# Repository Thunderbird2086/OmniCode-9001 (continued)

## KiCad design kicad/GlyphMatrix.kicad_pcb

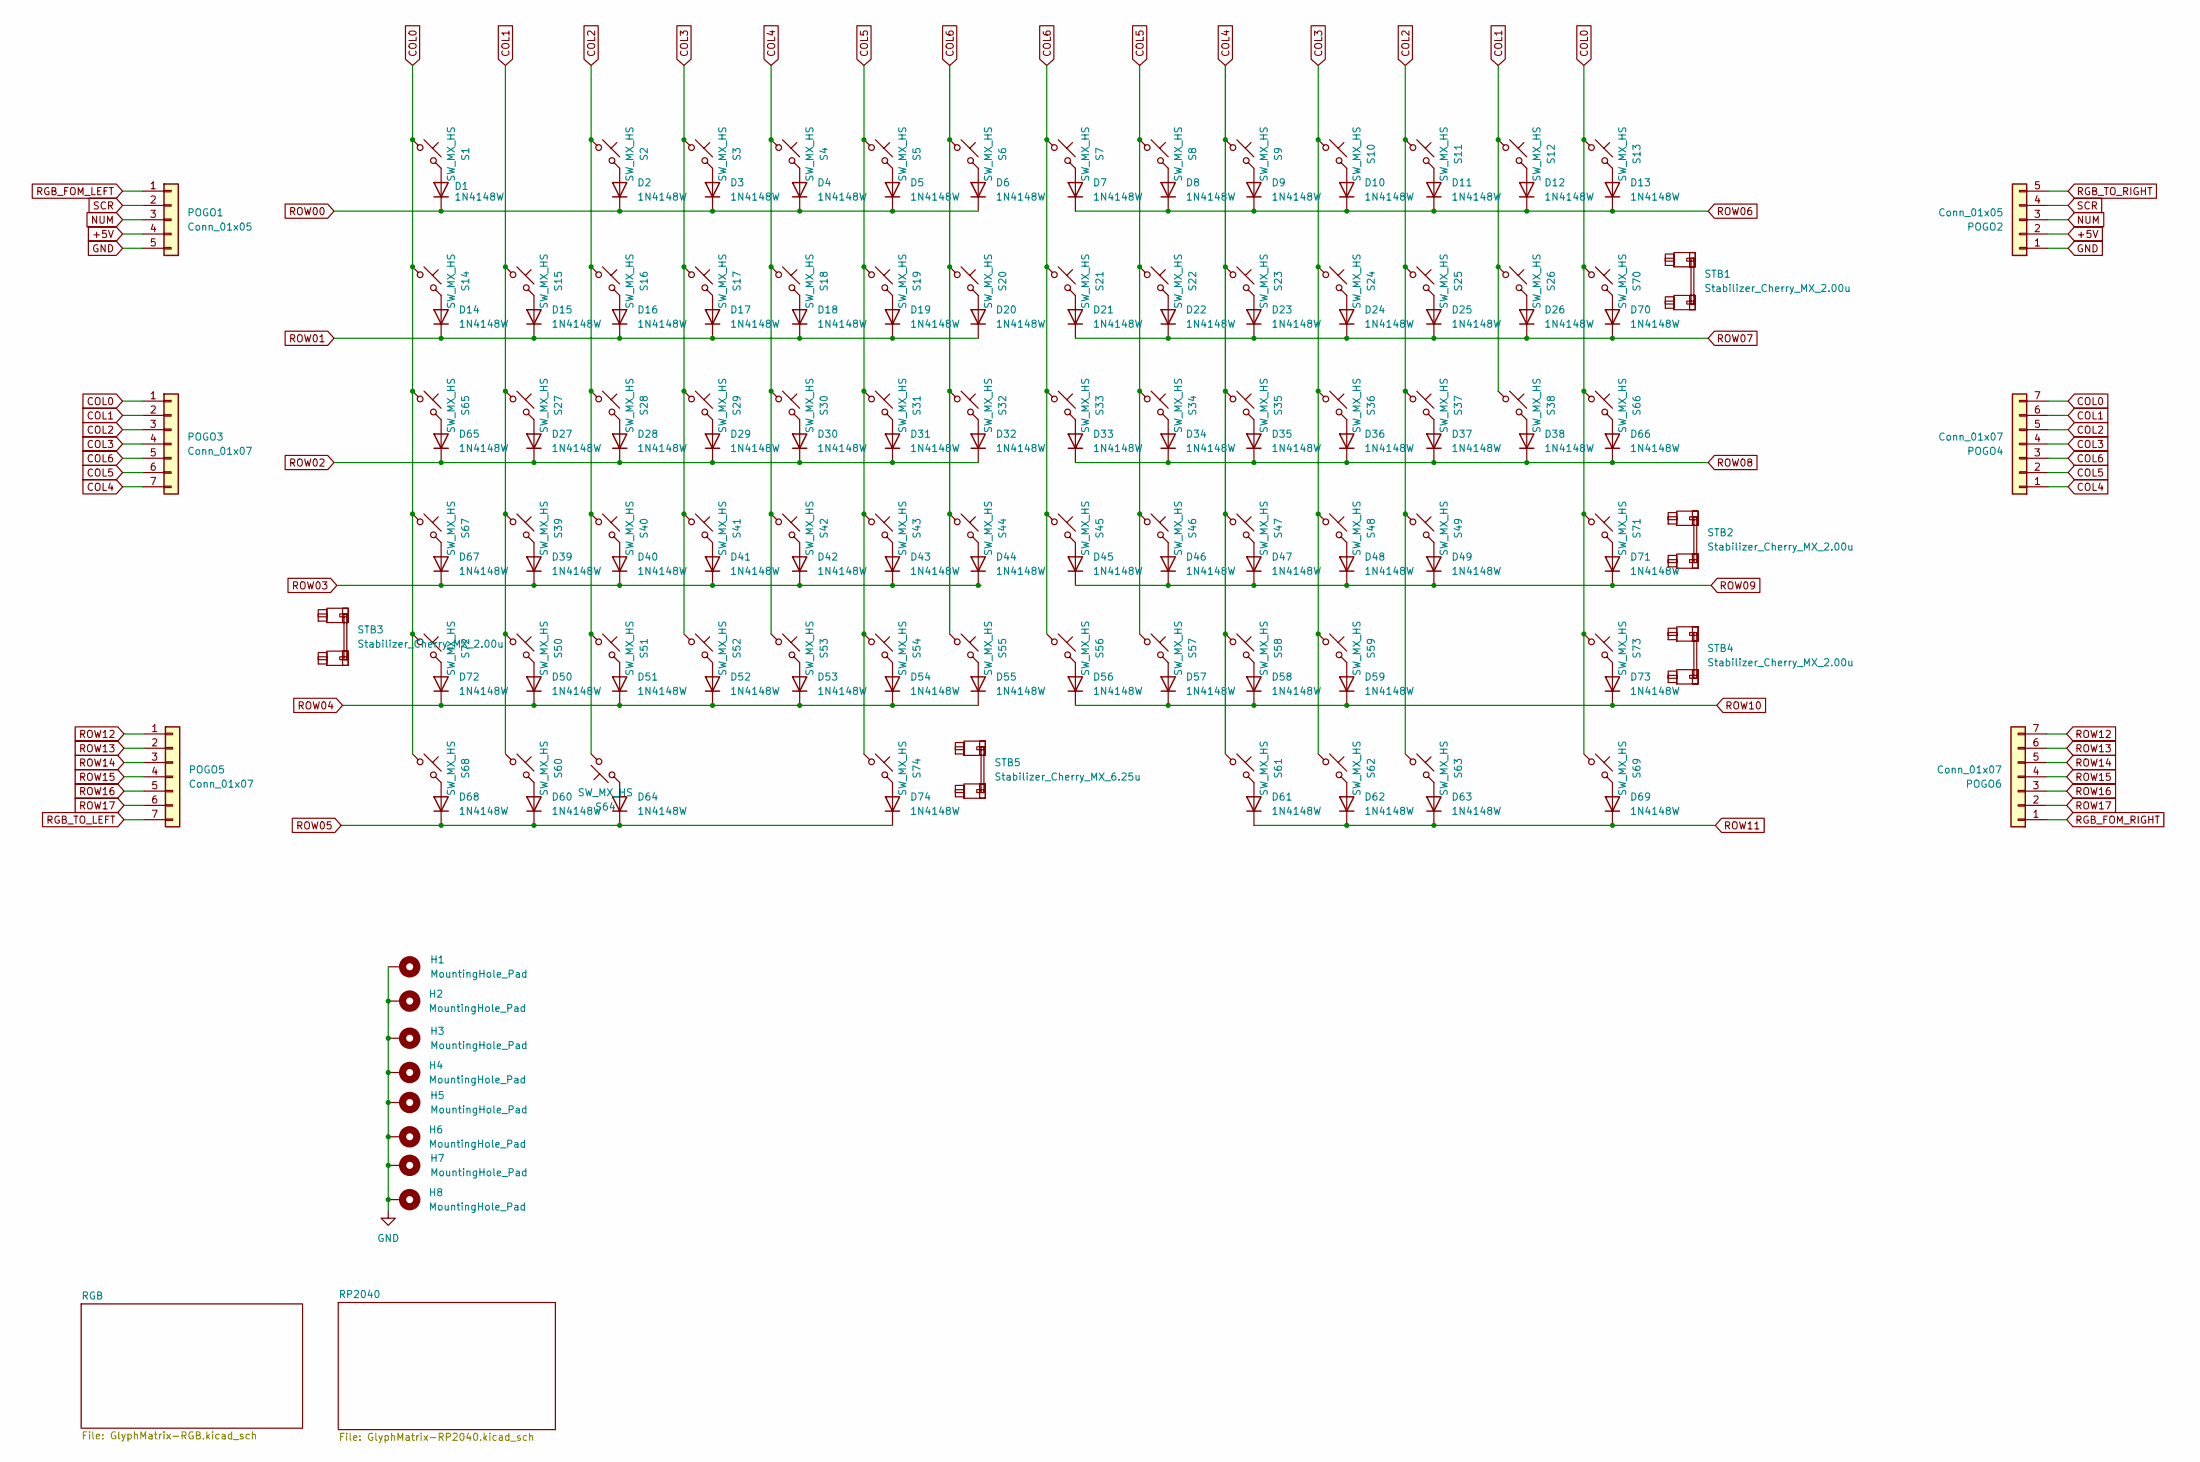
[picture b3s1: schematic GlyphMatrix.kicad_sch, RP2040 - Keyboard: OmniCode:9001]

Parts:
D1, D2, D3, D4, D5, D6, D7, D8, D9, D10, D11, D12, D13, D14, D15, D16, D17, D18, D19, D20, D21, D22, D23, D24, D25, D26, D27, D28, D29, D30, D31, D32, D33, D34, D35, D36, D37, D38, D39, D40, D41, D42, D43, D44, D45, D46, D47, D48, D49, D50, D51, D52, D53, D54, D55, D56, D57, D58, D59, D60, D61, D62, D63, D64, D65, D66, D67, D68, D69, D70, D71, D72, D73, D74: 1N4148W; D3_SMD; LCSC C7420318
H1, H2, H3, H4, H5, H6, H7, H8: MountingHole_Pad; MountingHole_3.2mm_Pad
POGO1, POGO2: Conn_01x05; Pogopin_1x05_P2.54mm_Curved
POGO3, POGO4, POGO5, POGO6: Conn_01x07; Pogopin_1x07_P2.54mm_Curved
S1, S2, S3, S4, S5, S6, S7, S8, S9, S10, S11, S12, S13, S14, S15, S16, S17, S18, S19, S20, S21, S22, S23, S24, S25, S26, S27, S28, S29, S30, S31, S32, S33, S34, S35, S36, S37, S38, S39, S40, S41, S42, S43, S44, S45, S46, S47, S48, S49, S50, S51, S52, S53, S54, S55, S56, S57, S58, S59, S60, S61, S62, S63: SW_MX_HS; SW_MX_HS_1u; LCSC C41430893
S64: SW_MX_HS; SW_MX_HS_1.25u; LCSC C41430893
S65, S66: SW_MX_HS; SW_MX_HS_1.5u; LCSC C41430893
S67, S68, S69: SW_MX_HS; SW_MX_HS_1.75u; LCSC C41430893
S70: SW_MX_HS; SW_MX_HS_2u; LCSC C41430893
S71, S72: SW_MX_HS; SW_MX_HS_2.25u; LCSC C41430893
S73: SW_MX_HS; SW_MX_HS_2.75u; LCSC C41430893
S74: SW_MX_HS; SW_MX_HS_6.25u; LCSC C41430893
STB1, STB2, STB3, STB4: Stabilizer_Cherry_MX_2.00u
STB5: Stabilizer_Cherry_MX_6.25u

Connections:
+5V: POGO1.4, POGO2.2; also elsewhere on the board
COL0: POGO3.1, POGO4.7, S1.2, S13.2, S14.2, S65.2, S66.2, S67.2, S68.2, S69.2, S70.2, S71.2, S72.2, S73.2; also elsewhere on the board
COL1: POGO3.2, POGO4.6, S12.2, S15.2, S26.2, S27.2, S38.2, S39.2, S50.2, S60.2; also elsewhere on the board
COL2: POGO3.3, POGO4.5, S2.2, S11.2, S16.2, S25.2, S28.2, S37.2, S40.2, S49.2, S51.2, S63.2, S64.2; also elsewhere on the board
COL3: POGO3.4, POGO4.4, S3.2, S10.2, S17.2, S24.2, S29.2, S36.2, S41.2, S48.2, S52.2, S59.2, S62.2; also elsewhere on the board
COL4: POGO3.7, POGO4.1, S4.2, S9.2, S18.2, S23.2, S30.2, S35.2, S42.2, S47.2, S53.2, S58.2, S61.2; also elsewhere on the board
COL5: POGO3.6, POGO4.2, S5.2, S8.2, S19.2, S22.2, S31.2, S34.2, S43.2, S46.2, S54.2, S57.2, S74.2; also elsewhere on the board
COL6: POGO3.5, POGO4.3, S6.2, S7.2, S20.2, S21.2, S32.2, S33.2, S44.2, S45.2, S55.2, S56.2; also elsewhere on the board
GND: H1.1, H2.1, H3.1, H4.1, H5.1, H6.1, H7.1, H8.1, POGO1.5, POGO2.1; also elsewhere on the board
NUM: POGO1.3, POGO2.3; also elsewhere on the board
unnamed: D1.2 (A), S1.1
unnamed: D2.2 (A), S2.1
unnamed: D3.2 (A), S3.1
unnamed: D4.2 (A), S4.1
unnamed: D5.2 (A), S5.1
unnamed: D6.2 (A), S6.1
unnamed: D7.2 (A), S7.1
unnamed: D8.2 (A), S8.1
unnamed: D9.2 (A), S9.1
unnamed: D10.2 (A), S10.1
unnamed: D11.2 (A), S11.1
unnamed: D12.2 (A), S12.1
unnamed: D13.2 (A), S13.1
unnamed: D14.2 (A), S14.1
unnamed: D15.2 (A), S15.1
unnamed: D16.2 (A), S16.1
unnamed: D17.2 (A), S17.1
unnamed: D18.2 (A), S18.1
unnamed: D19.2 (A), S19.1
unnamed: D20.2 (A), S20.1
unnamed: D21.2 (A), S21.1
unnamed: D22.2 (A), S22.1
unnamed: D23.2 (A), S23.1
unnamed: D24.2 (A), S24.1
unnamed: D25.2 (A), S25.1
unnamed: D26.2 (A), S26.1
unnamed: D27.2 (A), S27.1
unnamed: D28.2 (A), S28.1
unnamed: D29.2 (A), S29.1
unnamed: D30.2 (A), S30.1
unnamed: D31.2 (A), S31.1
unnamed: D32.2 (A), S32.1
unnamed: D33.2 (A), S33.1
unnamed: D34.2 (A), S34.1
unnamed: D35.2 (A), S35.1
unnamed: D36.2 (A), S36.1
unnamed: D37.2 (A), S37.1
unnamed: D38.2 (A), S38.1
unnamed: D39.2 (A), S39.1
unnamed: D40.2 (A), S40.1
unnamed: D41.2 (A), S41.1
unnamed: D42.2 (A), S42.1
unnamed: D43.2 (A), S43.1
unnamed: D44.2 (A), S44.1
unnamed: D45.2 (A), S45.1
unnamed: D46.2 (A), S46.1
unnamed: D47.2 (A), S47.1
unnamed: D48.2 (A), S48.1
unnamed: D49.2 (A), S49.1
unnamed: D50.2 (A), S50.1
unnamed: D51.2 (A), S51.1
unnamed: D52.2 (A), S52.1
unnamed: D53.2 (A), S53.1
unnamed: D54.2 (A), S54.1
unnamed: D55.2 (A), S55.1
unnamed: D56.2 (A), S56.1
unnamed: D57.2 (A), S57.1
unnamed: D58.2 (A), S58.1
unnamed: D59.2 (A), S59.1
unnamed: D60.2 (A), S60.1
unnamed: D61.2 (A), S61.1
unnamed: D62.2 (A), S62.1
unnamed: D63.2 (A), S63.1
unnamed: D64.2 (A), S64.1
unnamed: D65.2 (A), S65.1
unnamed: D66.2 (A), S66.1
unnamed: D67.2 (A), S67.1
unnamed: D68.2 (A), S68.1
unnamed: D69.2 (A), S69.1
unnamed: D70.2 (A), S70.1
unnamed: D71.2 (A), S71.1
unnamed: D72.2 (A), S72.1
unnamed: D73.2 (A), S73.1
unnamed: D74.2 (A), S74.1
RGB_FOM_LEFT: POGO1.1; also elsewhere on the board
RGB_FOM_RIGHT: POGO6.1; also elsewhere on the board
RGB_TO_LEFT: POGO5.7; also elsewhere on the board
RGB_TO_RIGHT: POGO2.5; also elsewhere on the board
ROW00: D1.1 (K), D2.1 (K), D3.1 (K), D4.1 (K), D5.1 (K), D6.1 (K); also elsewhere on the board
ROW01: D14.1 (K), D15.1 (K), D16.1 (K), D17.1 (K), D18.1 (K), D19.1 (K), D20.1 (K); also elsewhere on the board
ROW02: D27.1 (K), D28.1 (K), D29.1 (K), D30.1 (K), D31.1 (K), D32.1 (K), D65.1 (K); also elsewhere on the board
ROW03: D39.1 (K), D40.1 (K), D41.1 (K), D42.1 (K), D43.1 (K), D44.1 (K), D67.1 (K); also elsewhere on the board
ROW04: D50.1 (K), D51.1 (K), D52.1 (K), D53.1 (K), D54.1 (K), D55.1 (K), D72.1 (K); also elsewhere on the board
ROW05: D60.1 (K), D64.1 (K), D68.1 (K), D74.1 (K); also elsewhere on the board
ROW06: D7.1 (K), D8.1 (K), D9.1 (K), D10.1 (K), D11.1 (K), D12.1 (K), D13.1 (K); also elsewhere on the board
ROW07: D21.1 (K), D22.1 (K), D23.1 (K), D24.1 (K), D25.1 (K), D26.1 (K), D70.1 (K); also elsewhere on the board
ROW08: D33.1 (K), D34.1 (K), D35.1 (K), D36.1 (K), D37.1 (K), D38.1 (K), D66.1 (K); also elsewhere on the board
ROW09: D45.1 (K), D46.1 (K), D47.1 (K), D48.1 (K), D49.1 (K), D71.1 (K); also elsewhere on the board
ROW10: D56.1 (K), D57.1 (K), D58.1 (K), D59.1 (K), D73.1 (K); also elsewhere on the board
ROW11: D61.1 (K), D62.1 (K), D63.1 (K), D69.1 (K); also elsewhere on the board
ROW12: POGO5.1, POGO6.7; also elsewhere on the board
ROW13: POGO5.2, POGO6.6; also elsewhere on the board
ROW14: POGO5.3, POGO6.5; also elsewhere on the board
ROW15: POGO5.4, POGO6.4; also elsewhere on the board
ROW16: POGO5.5, POGO6.3; also elsewhere on the board
ROW17: POGO5.6, POGO6.2; also elsewhere on the board
SCR: POGO1.2, POGO2.4; also elsewhere on the board

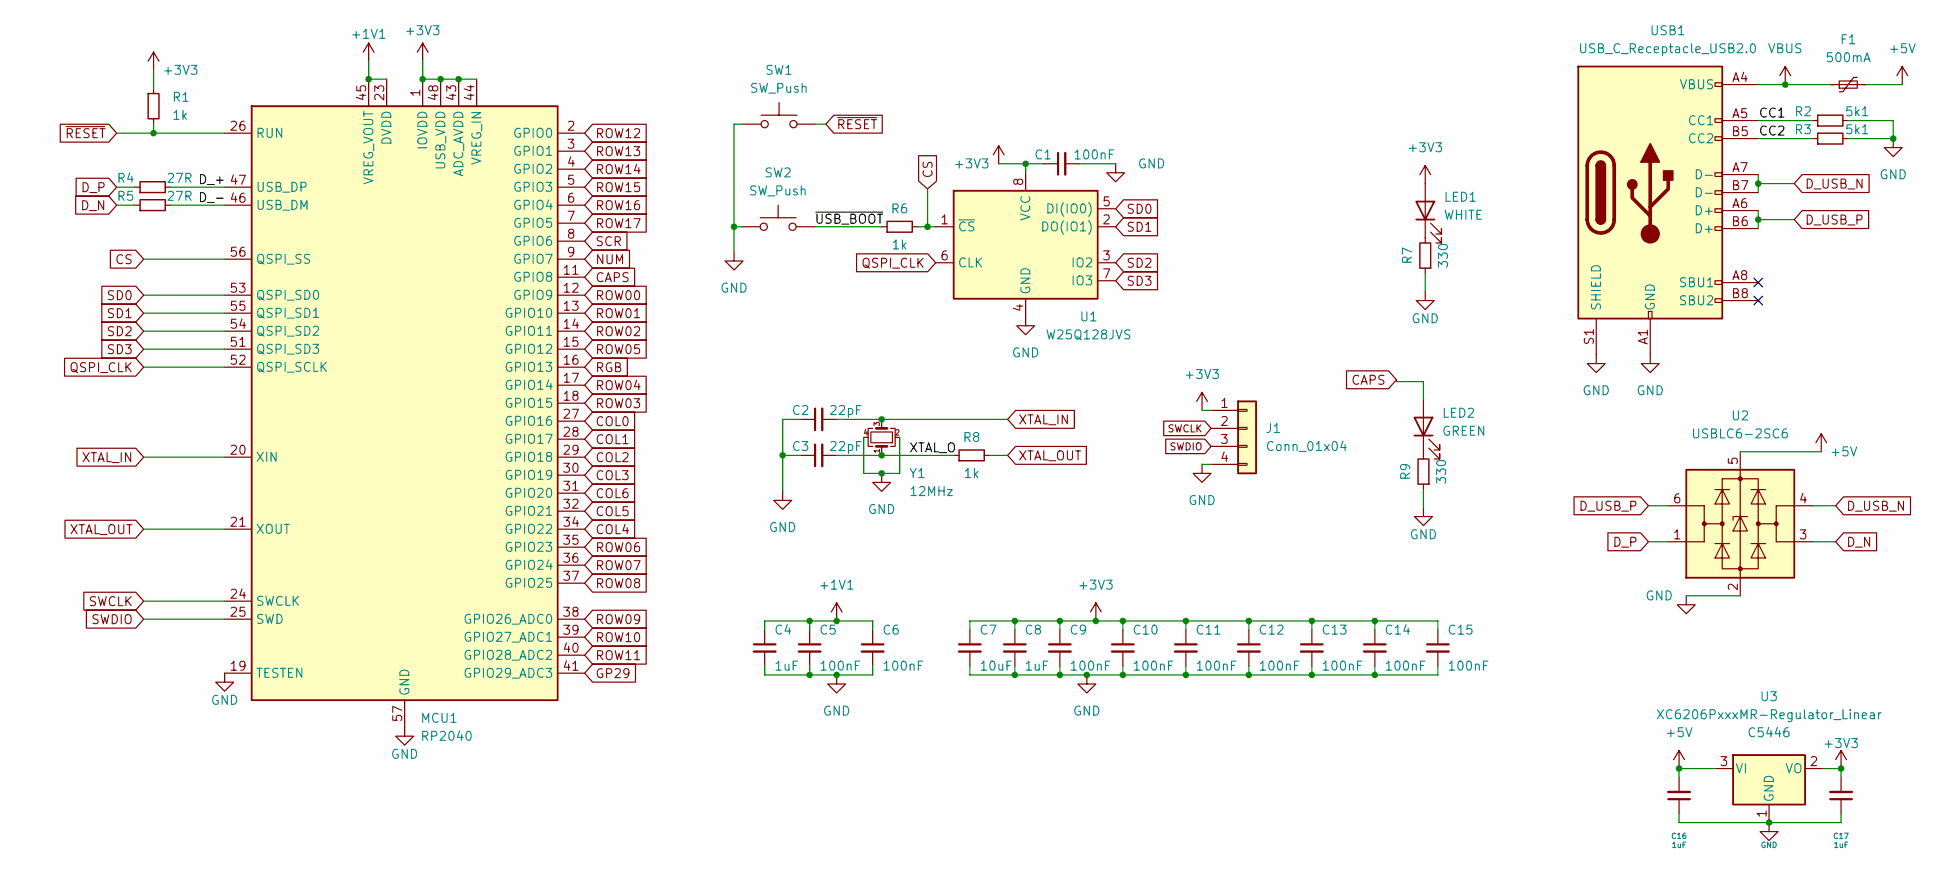
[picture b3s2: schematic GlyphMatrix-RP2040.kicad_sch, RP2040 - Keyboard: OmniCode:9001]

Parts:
C1, C5, C6, C9, C10, C11, C12, C13, C14, C15: 100nF; C_0402_1005Metric; LCSC C1525
C2, C3: 22pF; C_0402_1005Metric; LCSC C1555
C4, C8, C16, C17: 1uF; C_0402_1005Metric; LCSC C52923
C7: 10uF; C_0402_1005Metric; LCSC C15525
F1: 500mA; Fuse_1206_3216Metric; LCSC C70076
J1: Conn_01x04; PinHeader_2x02_P2.00mm_Vertical_SMD
LED1: WHITE; LED_0603_1608Metric_Pad1.05x0.95mm_HandSolder; LCSC C965808
LED2: GREEN; LED_0603_1608Metric_Pad1.05x0.95mm_HandSolder; LCSC C965805
MCU1: RP2040; RP2040-QFN-56; LCSC C2040
R1, R6, R8: 1k; R_0402_1005Metric; LCSC C11702
R2, R3: 5k1; R_0402_1005Metric; LCSC C25905
R4, R5: 27R; R_0603_1608Metric; LCSC C25190
R7, R9: 330; R_0603_1608Metric; LCSC C23138
SW1, SW2: SW_Push; SW_SPST_SKQG_WithoutStem; LCSC C202424
U1: W25Q128JVS; SOIC-8_5.3x5.3mm_P1.27mm; LCSC C131025
U2: USBLC6-2SC6; SOT-23-6; LCSC C2827654
U3: XC6206PxxxMR-Regulator_Linear; SOT-23; LCSC C5446
USB1: USB_C_Receptacle_USB2.0; GCT_USB4520-03-0-A_REVA; LCSC C2906290
Y1: 12MHz; Crystal_SMD_3225-4Pin_3.2x2.5mm; LCSC C9002

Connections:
+1V1: C4.1, C5.1, C6.1, MCU1.23 (DVDD), MCU1.45 (VREG_VOUT), MCU1.50 (DVDD)
+3V3: C1.1, C7.1, C8.1, C9.1, C10.1, C11.1, C12.1, C13.1, C14.1, C15.1, C17.2, J1.1, LED1.2 (A), MCU1.1 (IOVDD), MCU1.10 (IOVDD), MCU1.22 (IOVDD), MCU1.33 (IOVDD), MCU1.42 (IOVDD), MCU1.43 (ADC_AVDD), MCU1.44 (VREG_IN), MCU1.48 (USB_VDD), MCU1.49 (IOVDD), R1.1, U1.8 (VCC), U3.2 (VO)
+5V: C16.2, F1.2, U2.5 (VBUS), U3.3 (VI); also elsewhere on the board
/RP2040/CC1: R2.1, USB1.A5 (CC1)
/RP2040/CC2: R3.1, USB1.B5 (CC2)
/RP2040/D_+: MCU1.47 (USB_DP), R4.2
/RP2040/D_-: MCU1.46 (USB_DM), R5.2
/RP2040/XTAL_O: C3.2, R8.1, Y1.1
/RP2040/~USB_BOOT: R6.1, SW2.2
CAPS: LED2.2 (A), MCU1.11 (GPIO8)
COL0: MCU1.27 (GPIO16); also elsewhere on the board
COL1: MCU1.28 (GPIO17); also elsewhere on the board
COL2: MCU1.29 (GPIO18); also elsewhere on the board
COL3: MCU1.30 (GPIO19); also elsewhere on the board
COL4: MCU1.34 (GPIO22); also elsewhere on the board
COL5: MCU1.32 (GPIO21); also elsewhere on the board
COL6: MCU1.31 (GPIO20); also elsewhere on the board
CS: MCU1.56 (QSPI_SS), R6.2, U1.1 (~CS)
D_N: R5.1, U2.3 (I/O2)
D_P: R4.1, U2.1 (I/O1)
D_USB_N: U2.4 (I/O2), USB1.A7 (D-), USB1.B7 (D-)
D_USB_P: U2.6 (I/O1), USB1.A6 (D+), USB1.B6 (D+)
GND: C1.2, C2.1, C3.1, C4.2, C5.2, C6.2, C7.2, C8.2, C9.2, C10.2, C11.2, C12.2, C13.2, C14.2, C15.2, C16.1, C17.1, J1.4, MCU1.19 (TESTEN), MCU1.57 (GND), R2.2, R3.2, R7.1, R9.1, SW1.1, SW2.1, U1.4 (GND), U2.2 (GND), U3.1 (GND), USB1.A1 (GND), USB1.A12 (GND), USB1.B1 (GND), USB1.B12 (GND), USB1.S1 (SHIELD), Y1.2, Y1.4; also elsewhere on the board
GP29: MCU1.41 (GPIO29_ADC3)
NUM: MCU1.9 (GPIO7); also elsewhere on the board
unnamed: LED1.1 (K), R7.2
unnamed: LED2.1 (K), R9.2
QSPI_CLK: MCU1.52 (QSPI_SCLK), U1.6 (CLK)
RGB: MCU1.16 (GPIO13); also elsewhere on the board
ROW00: MCU1.12 (GPIO9); also elsewhere on the board
ROW01: MCU1.13 (GPIO10); also elsewhere on the board
ROW02: MCU1.14 (GPIO11); also elsewhere on the board
ROW03: MCU1.18 (GPIO15); also elsewhere on the board
ROW04: MCU1.17 (GPIO14); also elsewhere on the board
ROW05: MCU1.15 (GPIO12); also elsewhere on the board
ROW06: MCU1.35 (GPIO23); also elsewhere on the board
ROW07: MCU1.36 (GPIO24); also elsewhere on the board
ROW08: MCU1.37 (GPIO25); also elsewhere on the board
ROW09: MCU1.38 (GPIO26_ADC0); also elsewhere on the board
ROW10: MCU1.39 (GPIO27_ADC1); also elsewhere on the board
ROW11: MCU1.40 (GPIO28_ADC2); also elsewhere on the board
ROW12: MCU1.2 (GPIO0); also elsewhere on the board
ROW13: MCU1.3 (GPIO1); also elsewhere on the board
ROW14: MCU1.4 (GPIO2); also elsewhere on the board
ROW15: MCU1.5 (GPIO3); also elsewhere on the board
ROW16: MCU1.6 (GPIO4); also elsewhere on the board
ROW17: MCU1.7 (GPIO5); also elsewhere on the board
SCR: MCU1.8 (GPIO6); also elsewhere on the board
SD0: MCU1.53 (QSPI_SD0), U1.5 (DI(IO0))
SD1: MCU1.55 (QSPI_SD1), U1.2 (DO(IO1))
SD2: MCU1.54 (QSPI_SD2), U1.3 (IO2)
SD3: MCU1.51 (QSPI_SD3), U1.7 (IO3)
SWCLK: J1.2, MCU1.24 (SWCLK)
SWDIO: J1.3, MCU1.25 (SWD)
VBUS: F1.1, USB1.A4 (VBUS), USB1.A9 (VBUS), USB1.B4 (VBUS), USB1.B9 (VBUS)
XTAL_IN: C2.2, MCU1.20 (XIN), Y1.3
XTAL_OUT: MCU1.21 (XOUT), R8.2
~RESET: MCU1.26 (RUN), R1.2, SW1.2
